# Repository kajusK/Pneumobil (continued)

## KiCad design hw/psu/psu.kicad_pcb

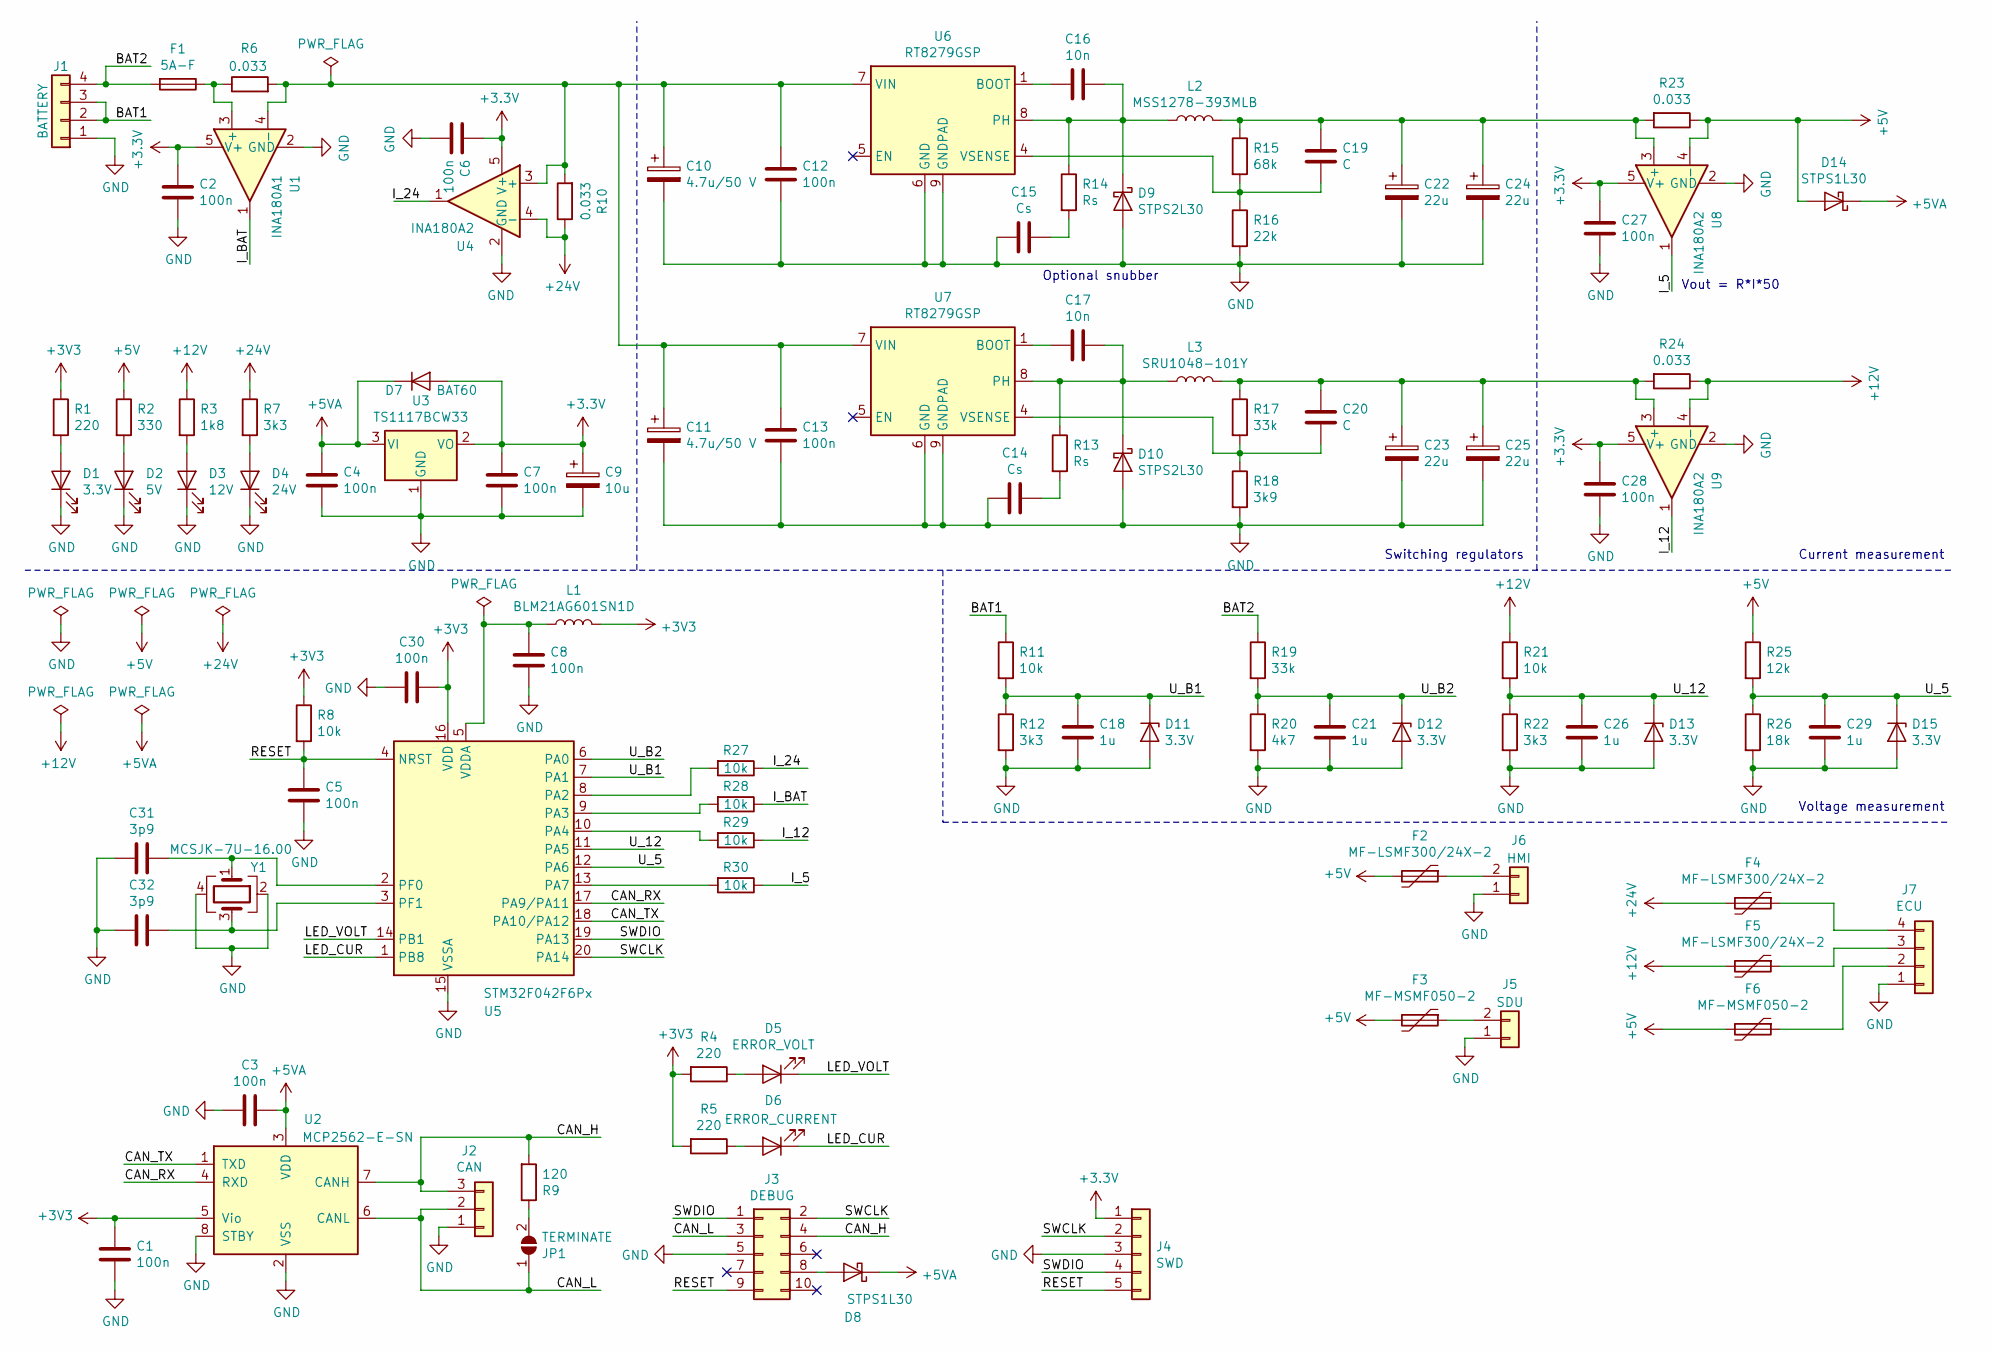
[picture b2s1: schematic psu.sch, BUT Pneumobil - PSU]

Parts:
C1, C2, C3, C4, C5, C6, C7, C8, C12, C13, C27, C28, C30: 100n; C_0805_2012Metric
C9: 10u; C_0805_2012Metric
C10, C11: 4.7u/50 V; C_0805_2012Metric
C14, C15: Cs; C_0805_2012Metric
C16, C17: 10n; C_0805_2012Metric
C18, C21, C26, C29: 1u; C_0805_2012Metric
C19, C20: C; C_0805_2012Metric
C22, C23, C24, C25: 22u; CP_Elec_5x5.8
C31, C32: 3p9; C_0805_2012Metric
D1: 3.3V; LED_1206_3216Metric
D2: 5V; LED_1206_3216Metric
D3: 12V; LED_1206_3216Metric
D4: 24V; LED_1206_3216Metric
D5: ERROR_VOLT; LED_1206_3216Metric
D6: ERROR_CURRENT; LED_1206_3216Metric
D7: BAT60; D_SOD-323
D8, D14: STPS1L30; D_SMB
D9, D10: STPS2L30; D_SMB
D11, D12, D13, D15: 3.3V; D_SOD-523
F1: 5A-F; Fuseholder_Cylinder-5x20mm_Schurter_0031_8201_Horizontal_Op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
F2, F4, F5: MF-LSMF300/24X-2; Fuse_2920_7451Metric
F3, F6: MF-MSMF050-2; Fuse_1812_4532Metric
J1: BATTERY; PhoenixContact_MCV_1,5_4-G-3.5_1x04_P3.50mm_Vertical
J2: CAN; Molex_Nano-Fit_105309-xx03_1x03_P2.50mm_Vertical
J3: DEBUG; IDC-Header_2x05_P2.54mm_Vertical
J4: SWD; PinHeader_1x05_P2.54mm_Vertical
J5: SDU; PhoenixContact_MCV_1,5_2-G-3.5_1x02_P3.50mm_Vertical
J6: HMI; PhoenixContact_MCV_1,5_2-G-3.5_1x02_P3.50mm_Vertical
J7: ECU; PhoenixContact_MCV_1,5_4-G-3.5_1x04_P3.50mm_Vertical
JP1: TERMINATE; SolderJumper-2_P1.3mm_Open_TrianglePad1.0x1.5mm
L1: BLM21AG601SN1D; L_0805_2012Metric
L2: MSS1278-393MLB; L_12x12mm_H8mm
L3: SRU1048-101Y; L_10.4x10.4_H4.8
R1, R4, R5: 220; R_0805_2012Metric
R2: 330; R_0805_2012Metric
R3: 1k8; R_0805_2012Metric
R6, R10, R23, R24: 0.033; R_1206_3216Metric
R7, R12, R22: 3k3; R_0805_2012Metric
R8, R11, R21, R27, R28, R29, R30: 10k; R_0805_2012Metric
R9: 120; R_0805_2012Metric
R13, R14: Rs; R_0805_2012Metric
R15: 68k; R_0805_2012Metric
R16: 22k; R_0805_2012Metric
R17, R19: 33k; R_0805_2012Metric
R18: 3k9; R_0805_2012Metric
R20: 4k7; R_0805_2012Metric
R25: 12k; R_0805_2012Metric
R26: 18k; R_0805_2012Metric
U1: INA180A1; SOT-23-5
U2: MCP2562-E-SN; SOIC-8_3.9x4.9mm_P1.27mm
U3: TS1117BCW33; SOT-223-3_TabPin2
U4, U8, U9: INA180A2; SOT-23-5
U5: STM32F042F6Px; TSSOP-20_4.4x6.5mm_P0.65mm
U6, U7: RT8279GSP; TI_SO-PowerPAD-8_ThermalVias
Y1: MCSJK-7U-16.00; Crystal_SMD_3225-4Pin_3.2x2.5mm

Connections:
+5V: D14.2 (A), F2.2, F3.2, F6.2, R2.1, R23.1, R25.1, U8.4 (-)
+5VA: C3.1, C4.1, D7.1 (K), D8.1 (K), D14.1 (K), U2.3 (VDD), U3.3 (VI)
+12V: F5.2, R3.1, R21.1, R24.1, U9.4 (-)
+24V: F4.2, R7.1, R10.1, U4.4 (-)
/BAT1: J1.2, J1.3, R11.1
/BAT2: F1.2, J1.4, R19.1
/CAN_H: J2.3, J3.4, R9.2, U2.7 (CANH)
/CAN_L: J2.2, J3.3, JP1.1 (A), U2.6 (CANL)
/CAN_RX: U2.4 (RXD), U5.17 (PA9/PA11)
/CAN_TX: U2.1 (TXD), U5.18 (PA10/PA12)
/I_5: R30.1, U8.1
/I_12: R29.1, U9.1
/I_24: R27.1, U4.1
/I_BAT: R28.1, U1.1
/LED_CUR: D6.1 (K), U5.1 (PB8)
/LED_VOLT: D5.1 (K), U5.14 (PB1)
/RESET: C5.1, J3.9, J4.5, R8.2, U5.4 (NRST)
/SWCLK: J3.2, J4.2, U5.20 (PA14)
/SWDIO: J3.1, J4.4, U5.19 (PA13)
/U_5: C29.1, D15.1 (K), R25.2, R26.1, U5.12 (PA6)
/U_12: C26.1, D13.1 (K), R21.2, R22.1, U5.11 (PA5)
/U_B1: C18.1, D11.1 (K), R11.2, R12.1, U5.7 (PA1)
/U_B2: C21.1, D12.1 (K), R19.2, R20.1, U5.6 (PA0)
GND: C1.2, C2.2, C3.2, C4.2, C5.2, C6.2, C7.2, C8.2, C9.2, C10.2, C11.2, C12.2, C13.2, C14.2, C15.2, C18.2, C21.2, C22.2, C23.2, C24.2, C25.2, C26.2, C27.2, C28.2, C29.2, C30.2, C31.2, C32.2, D1.1 (K), D2.1 (K), D3.1 (K), D4.1 (K), D9.2 (A), D10.2 (A), D11.2 (A), D12.2 (A), D13.2 (A), D15.2 (A), J1.1, J2.1, J3.5, J4.3, J5.1, J6.1, J7.1, R12.2, R16.2, R18.2, R20.2, R22.2, R26.2, U1.2 (GND), U2.2 (VSS), U2.8 (STBY), U3.1 (GND), U4.2 (GND), U5.15 (VSSA), U6.6 (GND), U6.9 (GNDPAD), U7.6 (GND), U7.9 (GNDPAD), U8.2 (GND), U9.2 (GND), Y1.2, Y1.4
unnamed: C8.1, L1.1, U5.5 (VDDA)
unnamed: C10.1, C11.1, C12.1, C13.1, R6.2, R10.2, U1.4 (-), U4.3 (+), U6.7 (VIN), U7.7 (VIN)
unnamed: C14.1, R13.2
unnamed: C15.1, R14.2
unnamed: C16.1, D9.1 (K), L2.1, R14.1, U6.8 (PH)
unnamed: C16.2, U6.1 (BOOT)
unnamed: C17.1, D10.1 (K), L3.1, R13.1, U7.8 (PH)
unnamed: C17.2, U7.1 (BOOT)
unnamed: C19.1, C22.1, C24.1, L2.2, R15.1, R23.2, U8.3 (+)
unnamed: C19.2, R15.2, R16.1, U6.4 (VSENSE)
unnamed: C20.1, C23.1, C25.1, L3.2, R17.1, R24.2, U9.3 (+)
unnamed: C20.2, R17.2, R18.1, U7.4 (VSENSE)
unnamed: C31.1, U5.2 (PF0), Y1.1
unnamed: C32.1, U5.3 (PF1), Y1.3
unnamed: D1.2 (A), R1.2
unnamed: D2.2 (A), R2.2
unnamed: D3.2 (A), R3.2
unnamed: D4.2 (A), R7.2
unnamed: D5.2 (A), R4.1
unnamed: D6.2 (A), R5.1
unnamed: D8.2 (A), J3.8
unnamed: F1.1, R6.1, U1.3 (+)
unnamed: F2.1, J6.2
unnamed: F3.1, J5.2
unnamed: F4.1, J7.4
unnamed: F5.1, J7.3
unnamed: F6.1, J7.2
unnamed: JP1.2 (B), R9.1
unnamed: R27.2, U5.8 (PA2)
unnamed: R28.2, U5.9 (PA3)
unnamed: R29.2, U5.10 (PA4)
unnamed: R30.2, U5.13 (PA7)

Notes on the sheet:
Vout = R*I*50
Optional snubber
Current measurement
Voltage measurement
Switching regulators

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
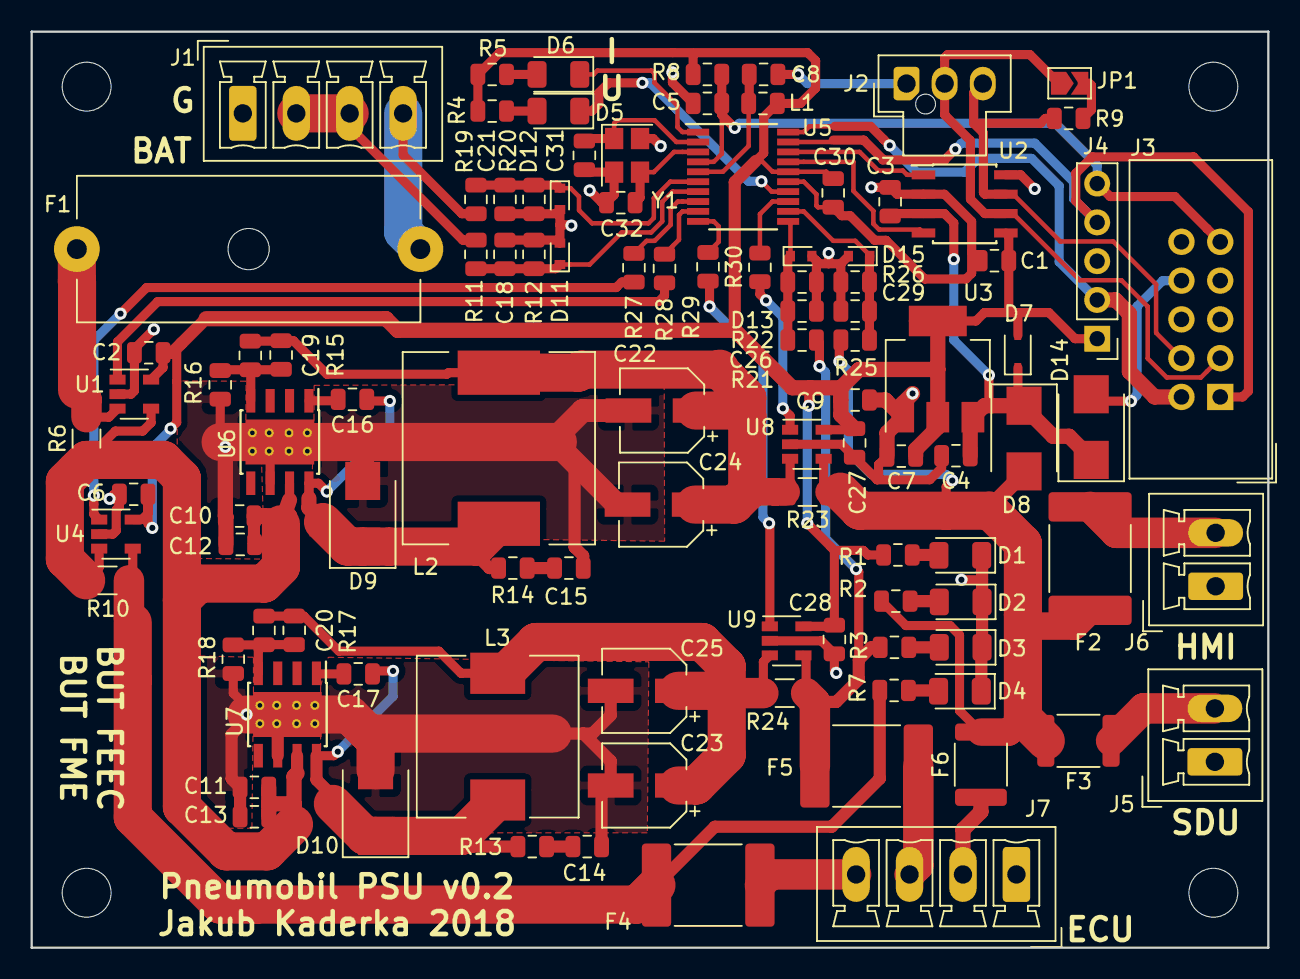
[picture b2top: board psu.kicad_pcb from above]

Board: 2 copper layers, 81.0 x 60.0 mm, 104 parts (0 on the bottom side), 57 nets.

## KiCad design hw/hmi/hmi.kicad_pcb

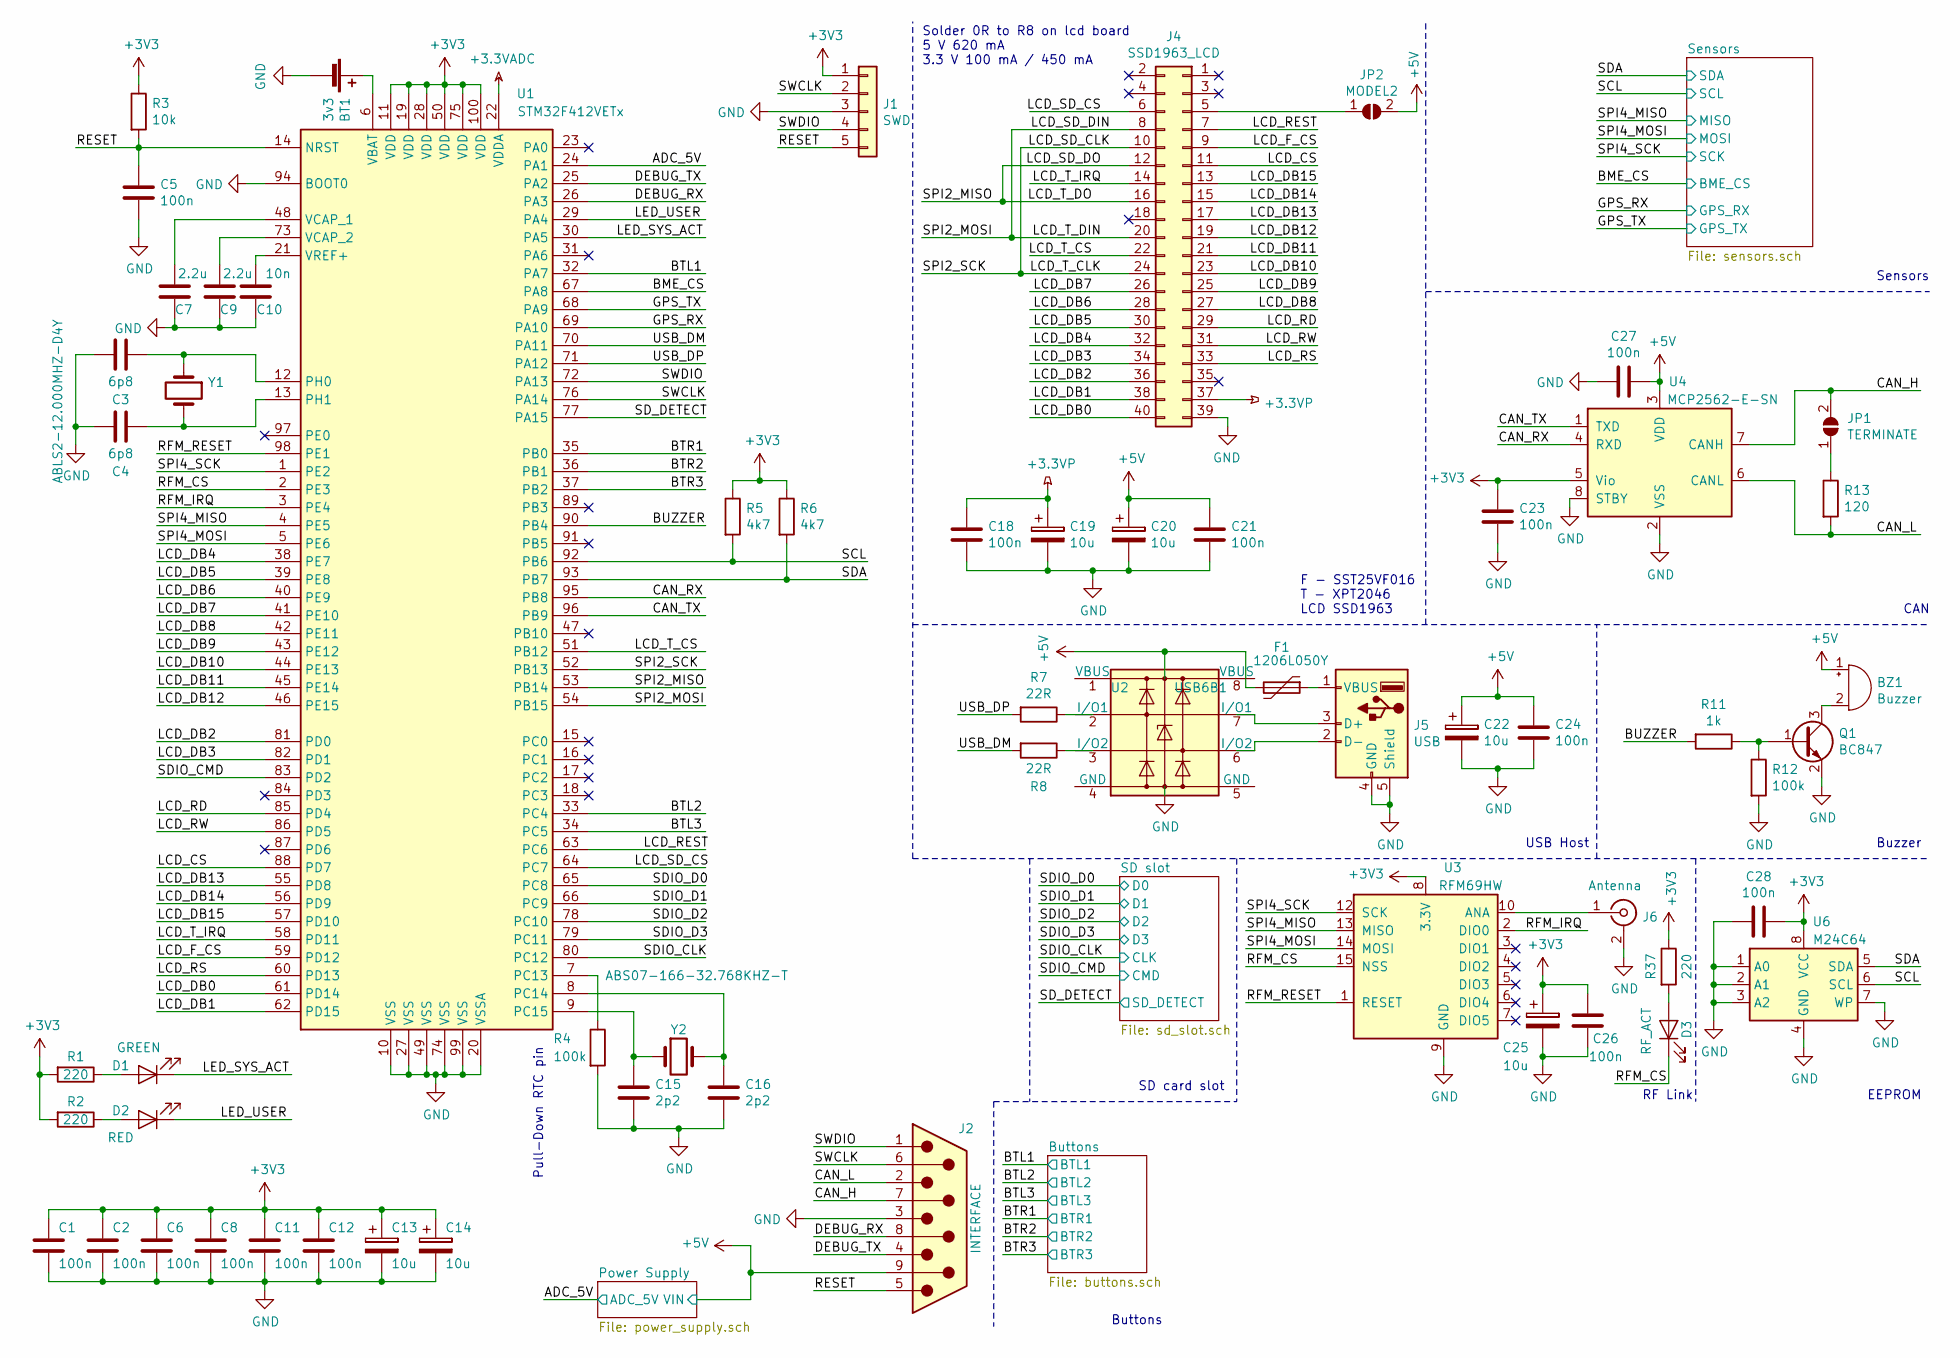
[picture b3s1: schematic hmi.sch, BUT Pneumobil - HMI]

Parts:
BT1: 3v3; BatteryHolder_Keystone_103_1x20mm
BZ1: Buzzer; MagneticBuzzer_ProSignal_ABI-009-RC
C1, C2, C5, C6, C8, C11, C12, C18, C21, C23, C24, C26, C27, C28: 100n; C_0805_2012Metric
C3, C4: 6p8; C_0805_2012Metric
C7, C9: 2.2u; C_0805_2012Metric
C10: 10n; C_0805_2012Metric
C13, C14, C19, C20, C22, C25: 10u; C_0805_2012Metric
C15, C16: 2p2; C_0805_2012Metric
D1: GREEN; LED_1206_3216Metric
D2: RED; LED_1206_3216Metric
D3: RF_ACT; LED_1206_3216Metric
F1: 1206L050Y; Fuse_1206_3216Metric
J1: SWD; PinHeader_1x05_P2.54mm_Horizontal
J2: INTERFACE; DSUB-9_Female_Vertical_P2.77x2.84mm_MountingHoles
J4: SSD1963_LCD; PinSocket_2x20_P2.54mm_Vertical
J5: USB; USB_A_Molex_105057_Vertical
J6: Antenna; SMA_Amphenol_132134-11_Vertical
JP1: TERMINATE; SolderJumper-2_P1.3mm_Open_TrianglePad1.0x1.5mm
JP2: MODEL2; SolderJumper-2_P1.3mm_Open_TrianglePad1.0x1.5mm
Q1: BC847; SOT-23
R1, R2, R37: 220; R_0805_2012Metric
R3: 10k; R_0805_2012Metric
R4, R12: 100k; R_0805_2012Metric
R5, R6: 4k7; R_0805_2012Metric
R7, R8: 22R; R_0805_2012Metric
R11: 1k; R_0805_2012Metric
R13: 120; R_0805_2012Metric
U1: STM32F412VETx; LQFP-100_14x14mm_P0.5mm
U2: USB6B1; SOIC-8_3.9x4.9mm_P1.27mm
U3: RFM69HW; HOPERF_RFM69HW
U4: MCP2562-E-SN; SOIC-8_3.9x4.9mm_P1.27mm
U6: M24C64; SOIC-8_3.9x4.9mm_P1.27mm
Y1: ABLS2-12.000MHZ-D4Y; Crystal_SMD_HC49-SD
Y2: ABS07-166-32.768KHZ-T; Crystal_SMD_3215-2Pin_3.2x1.5mm

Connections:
+3.3VADC: U1.22 (VDDA); also elsewhere on the board
+3.3VP: C18.1, C19.1, J4.37; also elsewhere on the board
+5V: BZ1.1 (-), C20.1, C21.1, C22.1, C24.1, C27.1, F1.2, J2.9, JP2.2 (B), U2.1 (VBUS), U2.8 (VBUS), U4.3 (VDD); also elsewhere on the board
/ADC_5V: U1.24 (PA1); also elsewhere on the board
/BME_CS: U1.67 (PA8); also elsewhere on the board
/BTL1: U1.32 (PA7); also elsewhere on the board
/BTL2: U1.33 (PC4); also elsewhere on the board
/BTL3: U1.34 (PC5); also elsewhere on the board
/BTR1: U1.35 (PB0); also elsewhere on the board
/BTR2: U1.36 (PB1); also elsewhere on the board
/BTR3: U1.37 (PB2); also elsewhere on the board
/BUZZER: R11.2, U1.90 (PB4)
/CAN_H: J2.7, JP1.2 (B), U4.7 (CANH)
/CAN_L: J2.2, R13.2, U4.6 (CANL)
/CAN_RX: U1.95 (PB8), U4.4 (RXD)
/CAN_TX: U1.96 (PB9), U4.1 (TXD)
/DEBUG_RX: J2.8, U1.26 (PA3)
/DEBUG_TX: J2.4, U1.25 (PA2)
/GPS_RX: U1.69 (PA10); also elsewhere on the board
/GPS_TX: U1.68 (PA9); also elsewhere on the board
/LCD_CS: J4.11, U1.88 (PD7)
/LCD_DB0: J4.40, U1.61 (PD14)
/LCD_DB1: J4.38, U1.62 (PD15)
/LCD_DB2: J4.36, U1.81 (PD0)
/LCD_DB3: J4.34, U1.82 (PD1)
/LCD_DB4: J4.32, U1.38 (PE7)
/LCD_DB5: J4.30, U1.39 (PE8)
/LCD_DB6: J4.28, U1.40 (PE9)
/LCD_DB7: J4.26, U1.41 (PE10)
/LCD_DB8: J4.27, U1.42 (PE11)
/LCD_DB9: J4.25, U1.43 (PE12)
/LCD_DB10: J4.23, U1.44 (PE13)
/LCD_DB11: J4.21, U1.45 (PE14)
/LCD_DB12: J4.19, U1.46 (PE15)
/LCD_DB13: J4.17, U1.55 (PD8)
/LCD_DB14: J4.15, U1.56 (PD9)
/LCD_DB15: J4.13, U1.57 (PD10)
/LCD_F_CS: J4.9, U1.59 (PD12)
/LCD_RD: J4.29, U1.85 (PD4)
/LCD_REST: J4.7, U1.63 (PC6)
/LCD_RS: J4.33, U1.60 (PD13)
/LCD_RW: J4.31, U1.86 (PD5)
/LCD_SD_CLK: J4.10, J4.24, U1.52 (PB13)
/LCD_SD_CS: J4.6, U1.64 (PC7)
/LCD_SD_DIN: J4.8, J4.20, U1.54 (PB15)
/LCD_SD_DO: J4.12, J4.16, U1.53 (PB14)
/LCD_T_CS: J4.22, U1.51 (PB12)
/LCD_T_IRQ: J4.14, U1.58 (PD11)
/LED_SYS_ACT: D1.1 (K), U1.30 (PA5)
/LED_USER: D2.1 (K), U1.29 (PA4)
/RESET: C5.1, J1.5, J2.5, R3.2, U1.14 (NRST)
/RFM_CS: D3.1 (K), U1.2 (PE3), U3.15 (NSS)
/RFM_IRQ: U1.3 (PE4), U3.2 (DIO0)
/RFM_RESET: U1.98 (PE1), U3.1 (RESET)
/SCL: R5.2, U1.92 (PB6), U6.6 (SCL); also elsewhere on the board
/SDA: R6.2, U1.93 (PB7), U6.5 (SDA); also elsewhere on the board
/SDIO_CLK: U1.80 (PC12); also elsewhere on the board
/SDIO_CMD: U1.83 (PD2); also elsewhere on the board
/SDIO_D0: U1.65 (PC8); also elsewhere on the board
/SDIO_D1: U1.66 (PC9); also elsewhere on the board
/SDIO_D2: U1.78 (PC10); also elsewhere on the board
/SDIO_D3: U1.79 (PC11); also elsewhere on the board
/SD_DETECT: U1.77 (PA15); also elsewhere on the board
/SPI4_MISO: U1.4 (PE5), U3.13 (MISO); also elsewhere on the board
/SPI4_MOSI: U1.5 (PE6), U3.14 (MOSI); also elsewhere on the board
/SPI4_SCK: U1.1 (PE2), U3.12 (SCK); also elsewhere on the board
/SWCLK: J1.2, J2.6, U1.76 (PA14)
/SWDIO: J1.4, J2.1, U1.72 (PA13)
/USB_DM: R8.2, U1.70 (PA11)
/USB_DP: R7.2, U1.71 (PA12)
GND: BT1.2 (-), C1.2, C2.2, C3.2, C4.2, C5.2, C6.2, C7.1, C8.2, C9.1, C10.2, C11.2, C12.2, C13.2, C14.2, C15.2, C16.2, C18.2, C19.2, C20.2, C21.2, C22.2, C23.2, C24.2, C25.2, C26.1, C27.2, C28.2, J1.3, J2.3, J4.39, J5.4 (GND), J5.5 (Shield), J6.2 (Ext), Q1.2 (E), R4.2, R12.2, U1.10 (VSS), U1.20 (VSSA), U1.27 (VSS), U1.49 (VSS), U1.74 (VSS), U1.94 (BOOT0), U1.99 (VSS), U2.4 (GND), U2.5 (GND), U3.9 (GND), U3.11 (GND), U4.2 (VSS), U4.8 (STBY), U6.1 (A0), U6.2 (A1), U6.3 (A2), U6.4 (GND), U6.7 (WP); also elsewhere on the board
unnamed: BT1.1 (+), U1.6 (VBAT)
unnamed: BZ1.2 (+), Q1.3 (C)
unnamed: C3.1, U1.12 (PH0), Y1.1
unnamed: C4.1, U1.13 (PH1), Y1.2
unnamed: C7.2, U1.48 (VCAP_1)
unnamed: C9.2, U1.73 (VCAP_2)
unnamed: C10.1, U1.21 (VREF+)
unnamed: C15.1, U1.9 (PC15), Y2.1
unnamed: C16.1, U1.8 (PC14), Y2.2
unnamed: D1.2 (A), R1.1
unnamed: D2.2 (A), R2.1
unnamed: D3.2 (A), R37.2
unnamed: F1.1, J5.1 (VBUS)
unnamed: J4.5, JP2.1 (A)
unnamed: J5.2 (D-), U2.6 (I/O2)
unnamed: J5.3 (D+), U2.7 (I/O1)
unnamed: J6.1 (In), U3.10 (ANA)
unnamed: JP1.1 (A), R13.1
unnamed: Q1.1 (B), R11.1, R12.1
unnamed: R4.1, U1.7 (PC13)
unnamed: R7.1, U2.2 (I/O1)
unnamed: R8.1, U2.3 (I/O2)

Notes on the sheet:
Solder 0R to R8 on lcd board 5 V 620 mA 3.3 V 100 mA / 450 mA
CAN
F - SST25VF016 T - XPT2046 LCD SSD1963
Buzzer
USB Host
EEPROM
RF Link
SD card slot
Pull-Down RTC pin
Buttons
Sensors

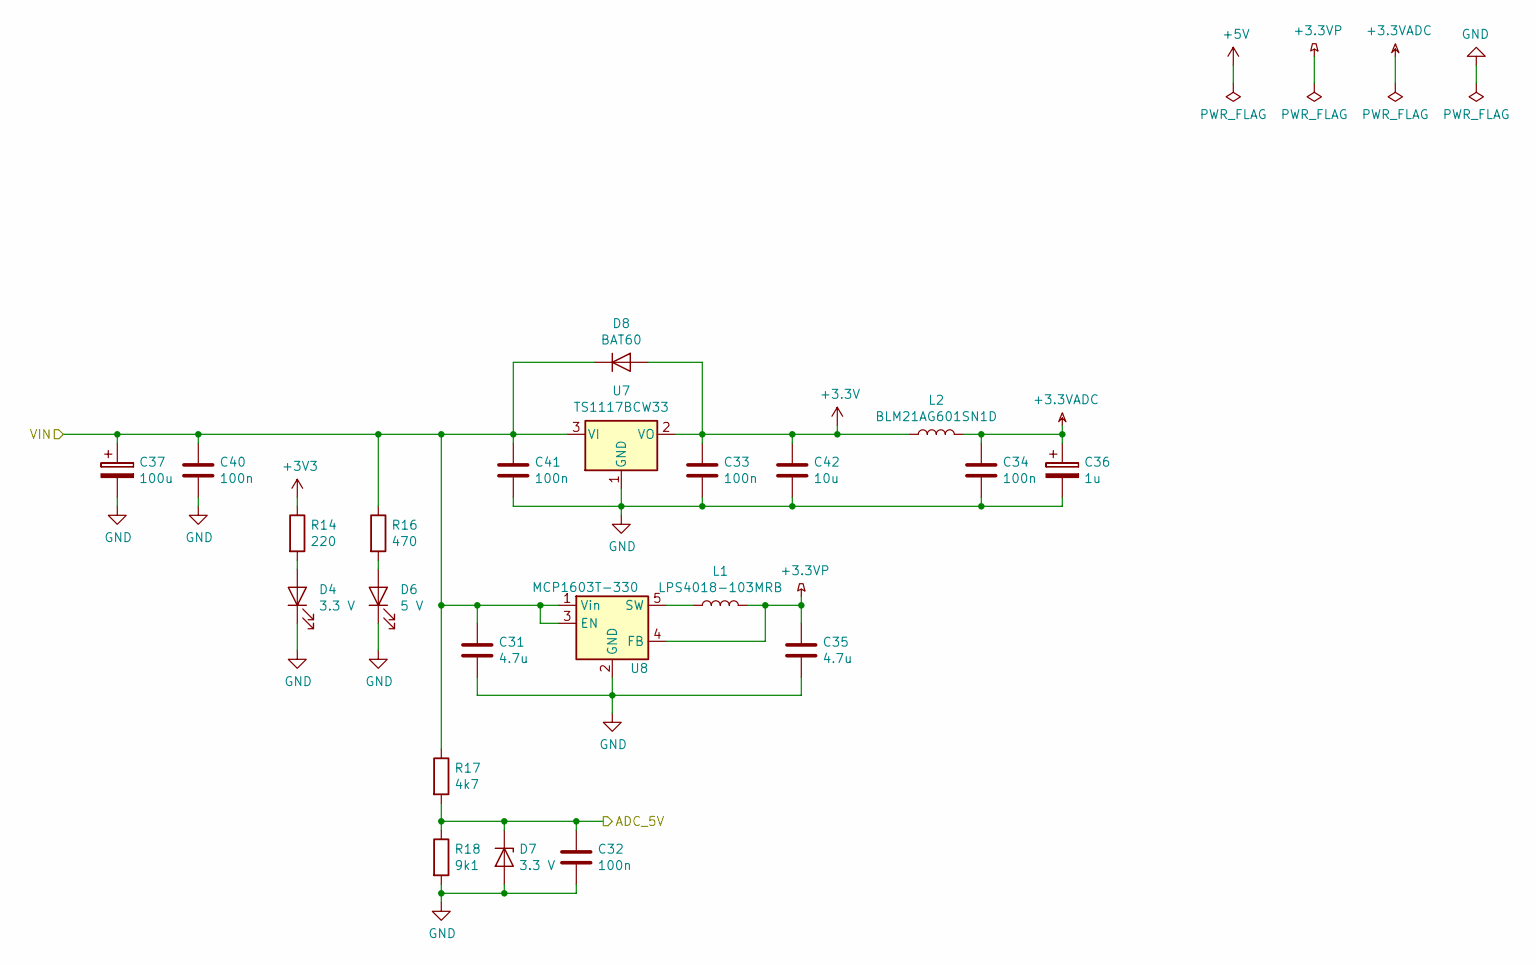
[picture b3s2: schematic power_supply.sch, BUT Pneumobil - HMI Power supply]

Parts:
C31, C35: 4.7u; C_0805_2012Metric
C32, C33, C34, C40, C41: 100n; C_0805_2012Metric
C36: 1u; C_0805_2012Metric
C37: 100u; CP_Elec_6.3x7.7
C42: 10u; C_0805_2012Metric
D4: 3.3 V; LED_1206_3216Metric
D6: 5 V; LED_1206_3216Metric
D7: 3.3 V; D_SOD-523
D8: BAT60; D_SOD-323
L1: LPS4018-103MRB; L_Coilcraft_LPS4018
L2: BLM21AG601SN1D; L_0805_2012Metric
R14: 220; R_0805_2012Metric
R16: 470; R_0805_2012Metric
R17: 4k7; R_0805_2012Metric
R18: 9k1; R_0805_2012Metric
U7: TS1117BCW33; SOT-223-3_TabPin2
U8: MCP1603T-330; TSOT-23-5

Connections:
+3.3VADC: C34.1, C36.1, L2.2; also elsewhere on the board
+3.3VP: C35.1, L1.2, U8.4 (FB); also elsewhere on the board
+5V: C31.1, C37.1, C40.1, C41.1, D8.1 (K), R16.1, R17.1, U7.3 (VI), U8.1 (Vin), U8.3 (EN); also elsewhere on the board
/ADC_5V: C32.1, D7.1 (K), R17.2, R18.1; also elsewhere on the board
GND: C31.2, C32.2, C33.2, C34.2, C35.2, C36.2, C37.2, C40.2, C41.2, C42.2, D4.1 (K), D6.1 (K), D7.2 (A), R18.2, U7.1 (GND), U8.2 (GND); also elsewhere on the board
unnamed: D4.2 (A), R14.2
unnamed: D6.2 (A), R16.2
unnamed: L1.1, U8.5 (SW)

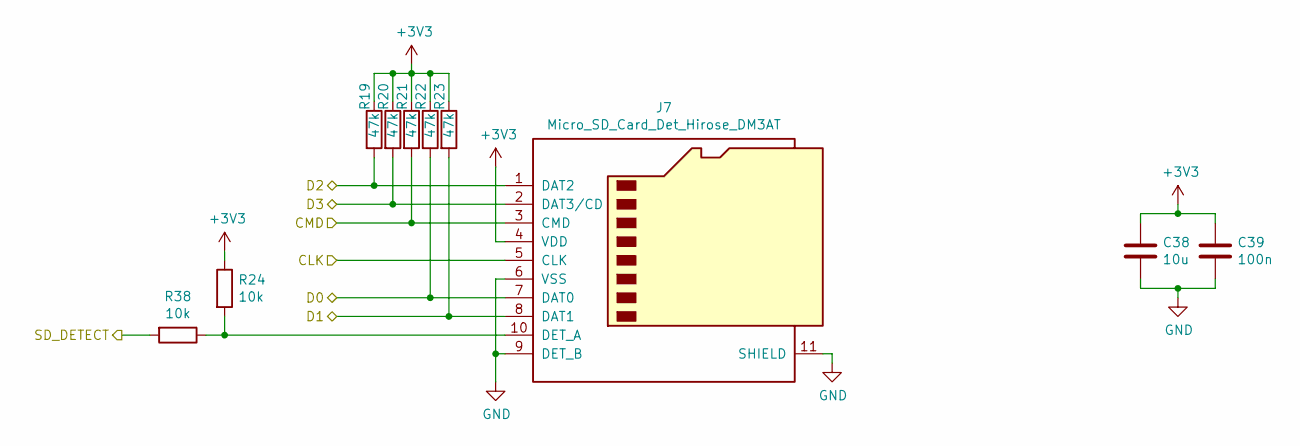
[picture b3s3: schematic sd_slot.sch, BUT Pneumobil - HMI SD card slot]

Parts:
C38: 10u; C_0805_2012Metric
C39: 100n; C_0805_2012Metric
J7: Micro_SD_Card_Det_Hirose_DM3AT; microSD_HC_Hirose_DM3AT-SF-PEJM5
R19, R20, R21, R22, R23: 47k; R_0805_2012Metric
R24, R38: 10k; R_0805_2012Metric

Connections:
/SDIO_CLK: J7.5 (CLK); also elsewhere on the board
/SDIO_CMD: J7.3 (CMD), R21.2; also elsewhere on the board
/SDIO_D0: J7.7 (DAT0), R22.2; also elsewhere on the board
/SDIO_D1: J7.8 (DAT1), R23.2; also elsewhere on the board
/SDIO_D2: J7.1 (DAT2), R19.2; also elsewhere on the board
/SDIO_D3: J7.2 (DAT3/CD), R20.2; also elsewhere on the board
/SD_DETECT: R38.2; also elsewhere on the board
GND: C38.2, C39.2, J7.6 (VSS), J7.9 (DET_B), J7.11 (SHIELD); also elsewhere on the board
unnamed: J7.10 (DET_A), R24.2, R38.1

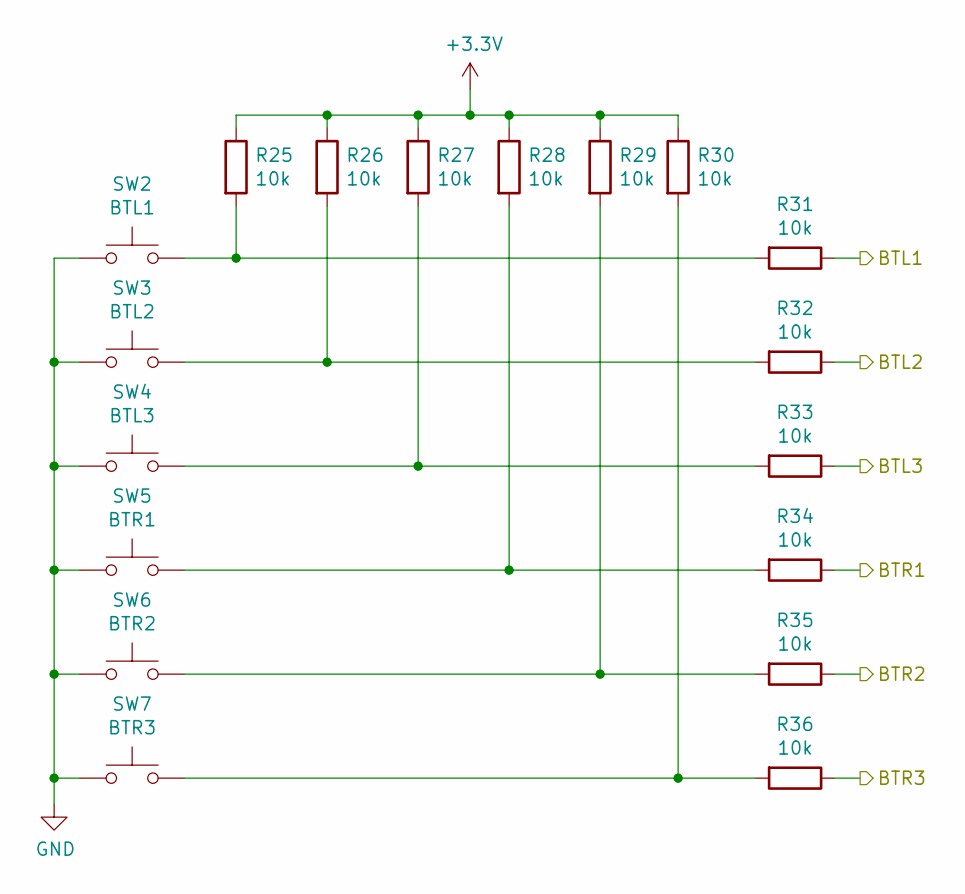
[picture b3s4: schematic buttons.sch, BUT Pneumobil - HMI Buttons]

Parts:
R25, R26, R27, R28, R29, R30, R31, R32, R33, R34, R35, R36: 10k; R_0805_2012Metric
SW2: BTL1; SW_SPST_PTS645
SW3: BTL2; SW_SPST_PTS645
SW4: BTL3; SW_SPST_PTS645
SW5: BTR1; SW_SPST_PTS645
SW6: BTR2; SW_SPST_PTS645
SW7: BTR3; SW_SPST_PTS645

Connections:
/BTL1: R31.1; also elsewhere on the board
/BTL2: R32.1; also elsewhere on the board
/BTL3: R33.1; also elsewhere on the board
/BTR1: R34.1; also elsewhere on the board
/BTR2: R35.1; also elsewhere on the board
/BTR3: R36.1; also elsewhere on the board
GND: SW2.1, SW3.1, SW4.1, SW5.1, SW6.1, SW7.1; also elsewhere on the board
unnamed: R25.2, R31.2, SW2.2
unnamed: R26.2, R32.2, SW3.2
unnamed: R27.2, R33.2, SW4.2
unnamed: R28.2, R34.2, SW5.2
unnamed: R29.2, R35.2, SW6.2
unnamed: R30.2, R36.2, SW7.2

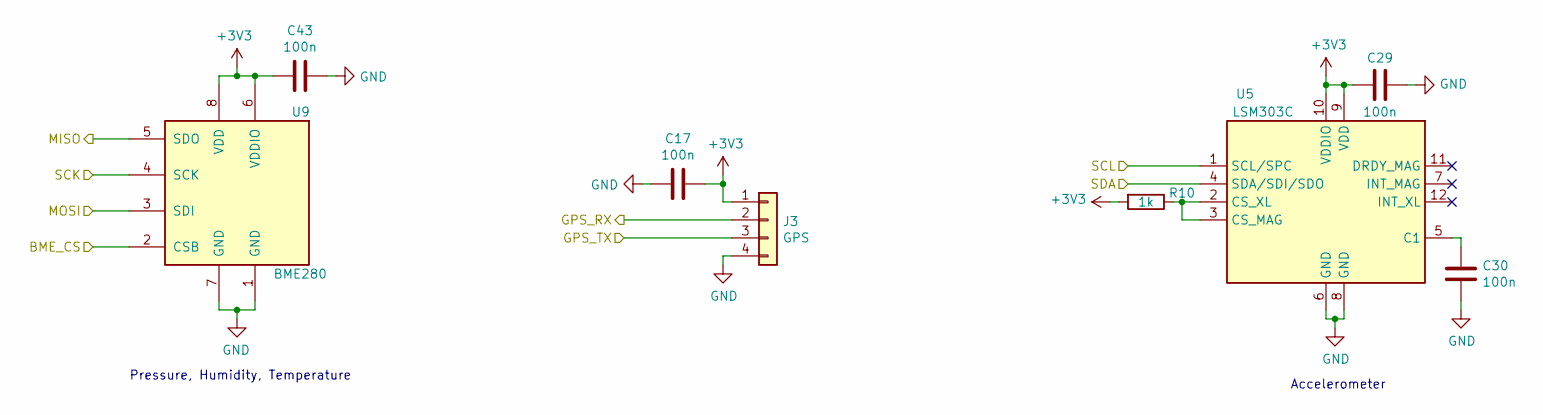
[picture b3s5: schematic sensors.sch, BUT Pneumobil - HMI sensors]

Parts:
C17, C29, C30, C43: 100n; C_0805_2012Metric
J3: GPS; Molex_KK-254_AE-6410-04A_1x04_P2.54mm_Vertical
R10: 1k; R_0805_2012Metric
U5: LSM303C; LGA-12_2x2mm_P0.5mm
U9: BME280; Bosch_LGA-8_2.5x2.5mm_P0.65mm_ClockwisePinNumbering

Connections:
/BME_CS: U9.2 (CSB); also elsewhere on the board
/GPS_RX: J3.2; also elsewhere on the board
/GPS_TX: J3.3; also elsewhere on the board
/SCL: U5.1 (SCL/SPC); also elsewhere on the board
/SDA: U5.4 (SDA/SDI/SDO); also elsewhere on the board
/SPI4_MISO: U9.5 (SDO); also elsewhere on the board
/SPI4_MOSI: U9.3 (SDI); also elsewhere on the board
/SPI4_SCK: U9.4 (SCK); also elsewhere on the board
GND: C17.2, C29.1, C30.2, C43.1, J3.4, U5.6 (GND), U5.8 (GND), U9.1 (GND), U9.7 (GND); also elsewhere on the board
unnamed: C30.1, U5.5 (C1)
unnamed: R10.1, U5.2 (CS_XL), U5.3 (CS_MAG)

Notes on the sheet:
Accelerometer
Pressure, Humidity, Temperature

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
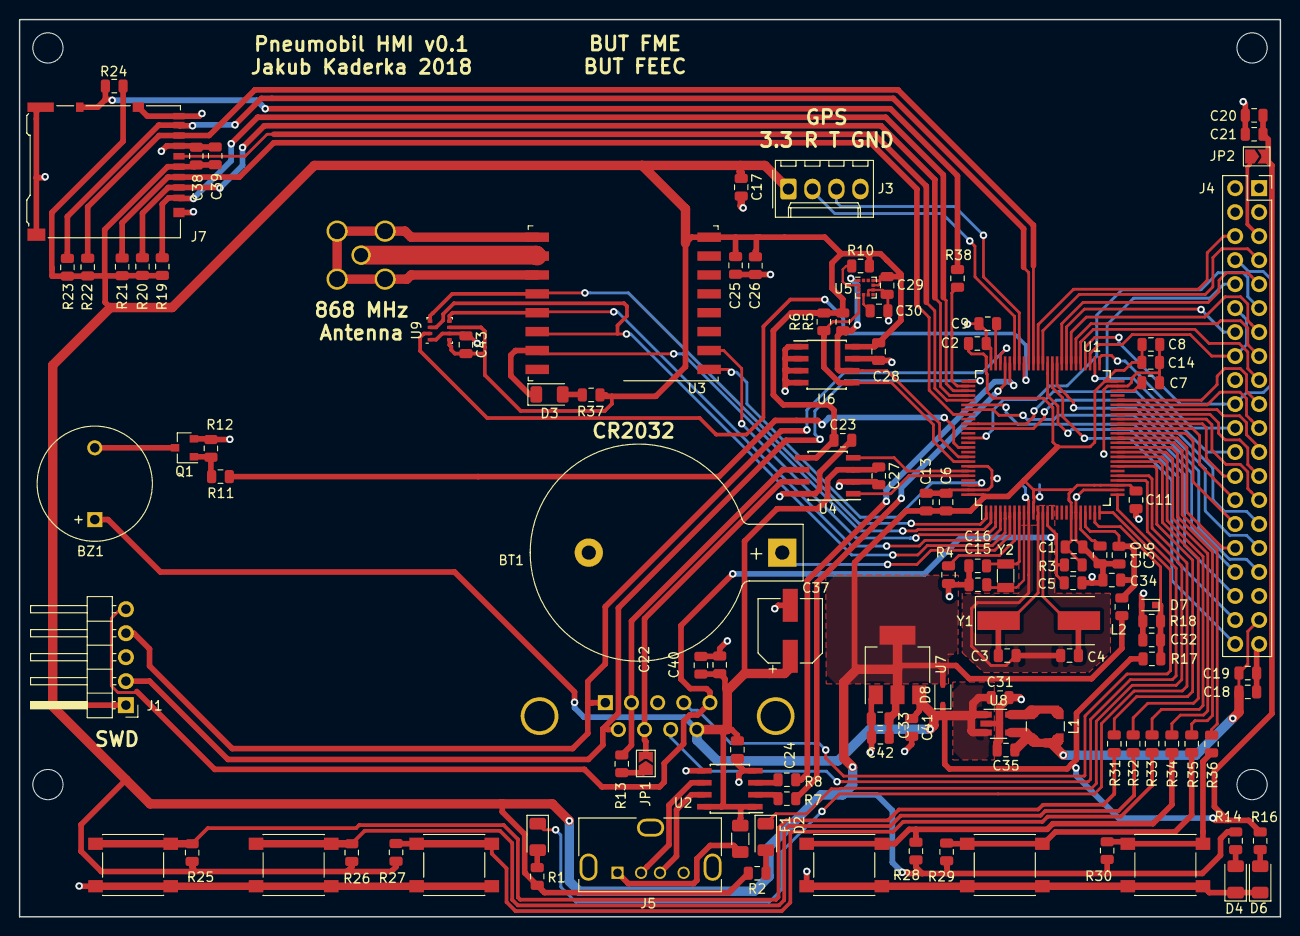
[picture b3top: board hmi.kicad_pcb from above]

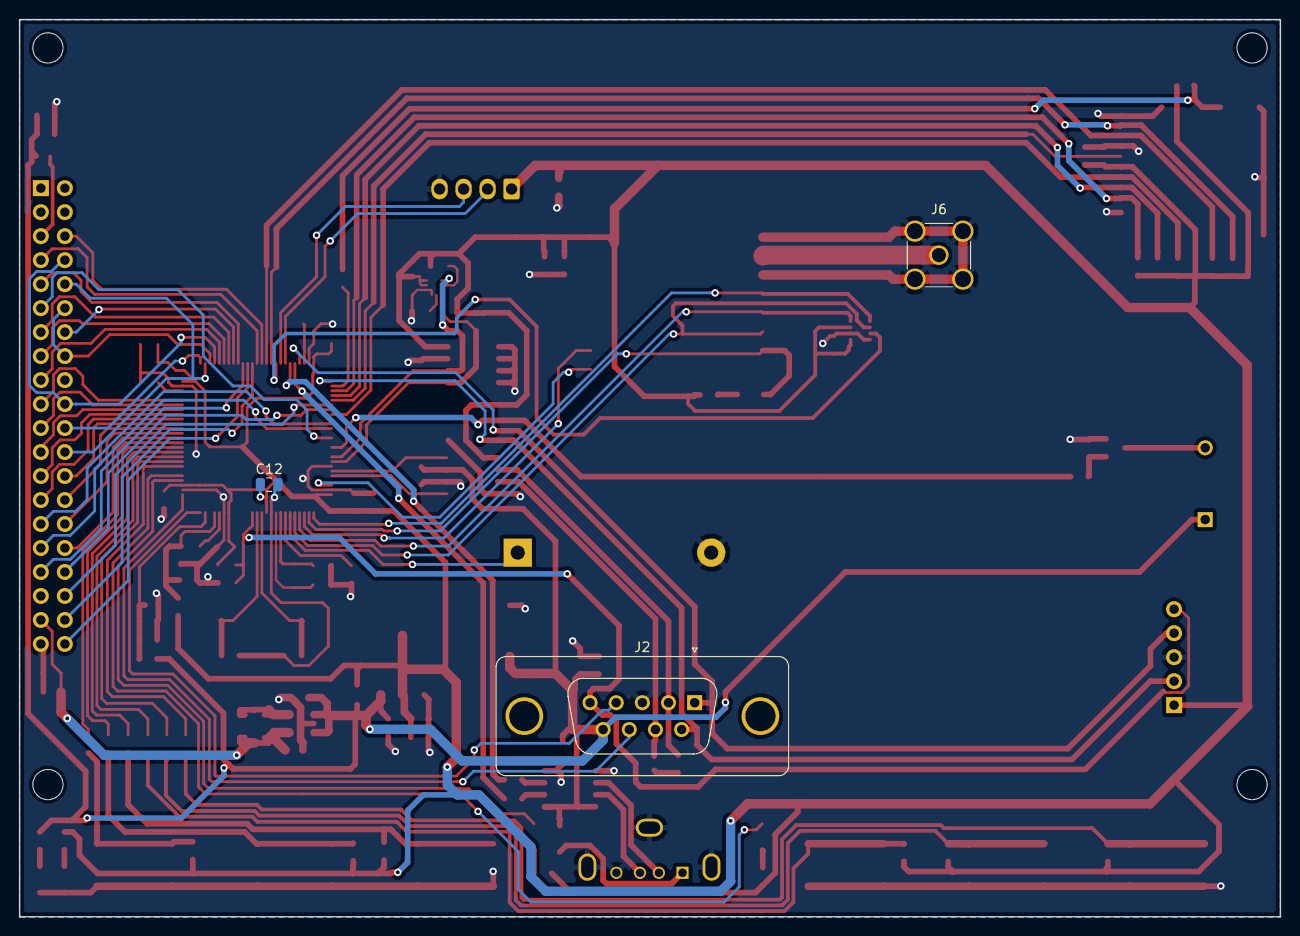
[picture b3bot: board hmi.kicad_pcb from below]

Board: 2 copper layers, 133.5 x 95.0 mm, 118 parts (3 on the bottom side), 106 nets.
